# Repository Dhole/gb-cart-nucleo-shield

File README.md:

# Game Boy Cart NUCLEO Shield

## Description

This is the design of a Shield for NUCLEO STM32 development boards (also known
as STM32 NUCLEO Morpho) to connect Game Boy cartridges.

This PCB is meant to be used with my Game Boy Cart reader/writer:

- [gb-rw-stm32f411](https://github.com/Dhole/gb-rw-stm32f411)
- [gb-rw-host](https://github.com/Dhole/gb-rw-host)

## Pictures

## Components

Prices are estimations taken from AliExpress (except when stated explicitly)

- 2 x 6 pin toggle switch (~ 2 x 1.3 EUR / 10)

- 2 x 40 pin header connector strip, 2.54m spacing (~ 2 x 1.03 EUR / 10)
  - You will need to cut the strips into: 2 x 17 pins, 2 x 19 pins

- 1 x GBA slot (~ 1 x 7.02 EUR / 5)

The firmware is implemented to work on the NUCLEO-F411RE

- 1 x NUCLEO-F411RE (1 x 11.48 EUR at [eu.mouser.com](https://eu.mouser.com))

I ordered the manufacture of the board at JLCPCB with great results
- 1 x 2 layer PCB board (~ 1 x 10 EUR / 10 with shipping included in 2018)

## Attributions

The design this PCB is based on an [STM32 NUCLEO Morpho template made by
mobilinkd](https://github.com/mobilinkd/stm-morpho-template) published under
the MIT License.

The Game Boy cartridge slot component used in the PCB is taken from the [KiCad libraries by gekkio](https://github.com/Gekkio/gekkio-kicad-libs) published under the 
[Creative Commons Attribution license](https://creativecommons.org/licenses/by/4.0/)

## License

I'm publishing the rest of the work under the [Creative Commons Attribution-ShareAlike license](https://creativecommons.org/licenses/by-sa/4.0/).

**CC BY-SA**

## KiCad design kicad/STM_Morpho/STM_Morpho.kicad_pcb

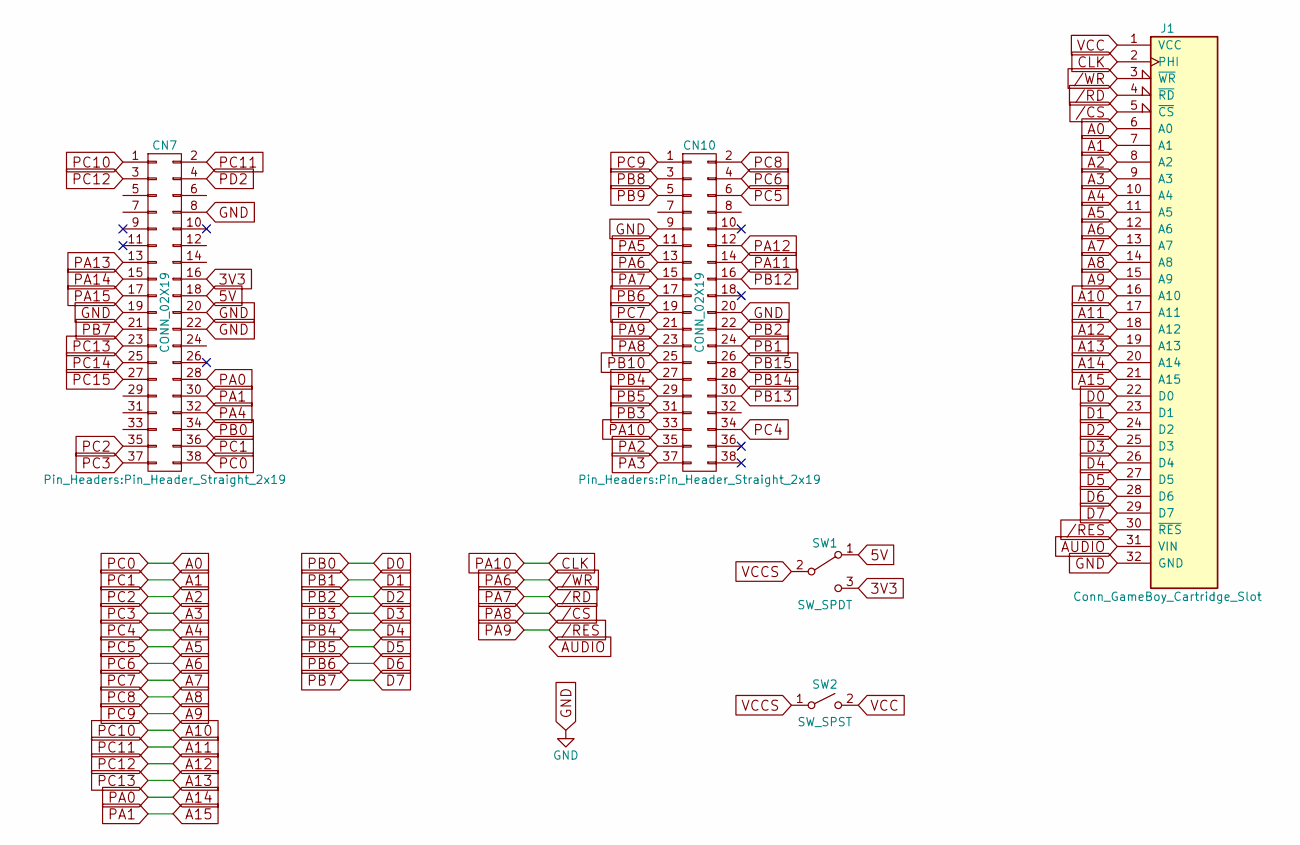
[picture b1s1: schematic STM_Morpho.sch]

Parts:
CN7, CN10: CONN_02X19; Pin_Header_Straight_2x19
J1: Conn_GameBoy_Cartridge_Slot; GameBoy_Cartridge_Slot_DSLite
SW1: SW_SPDT; SW_CuK_JS202011CQN_DPDT_Straight
SW2: SW_SPST; SW_CuK_JS202011CQN_DPDT_Straight

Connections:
3V3: CN7.16, SW1.3 (C)
5V: CN7.18, SW1.1 (A)
/CS: CN10.23, J1.5 (~CS)
/RD: CN10.15, J1.4 (~RD)
/RES: CN10.21, J1.30 (~RES)
/WR: CN10.13, J1.3 (~WR)
A0: CN7.38, J1.6 (A0)
A1: CN7.36, J1.7 (A1)
A2: CN7.35, J1.8 (A2)
A3: CN7.37, J1.9 (A3)
A4: CN10.34, J1.10 (A4)
A5: CN10.6, J1.11 (A5)
A6: CN10.4, J1.12 (A6)
A7: CN10.19, J1.13 (A7)
A8: CN10.2, J1.14 (A8)
A9: CN10.1, J1.15 (A9)
A10: CN7.1, J1.16 (A10)
A11: CN7.2, J1.17 (A11)
A12: CN7.3, J1.18 (A12)
A13: CN7.23, J1.19 (A13)
A14: CN7.28, J1.20 (A14)
A15: CN7.30, J1.21 (A15)
AUDIO: J1.31 (VIN)
CLK: CN10.33, J1.2 (PHI)
D0: CN7.34, J1.22 (D0)
D1: CN10.24, J1.23 (D1)
D2: CN10.22, J1.24 (D2)
D3: CN10.31, J1.25 (D3)
D4: CN10.27, J1.26 (D4)
D5: CN10.29, J1.27 (D5)
D6: CN10.17, J1.28 (D6)
D7: CN7.21, J1.29 (D7)
GND: CN7.8, CN7.19, CN7.20, CN7.22, CN10.9, CN10.20, J1.32 (GND)
PA4: CN7.32
PA5: CN10.11
PA11: CN10.14
PA12: CN10.12
PA13: CN7.13
PA14: CN7.15
PA15: CN7.17
PB8: CN10.3
PB9: CN10.5
PB10: CN10.25
PB12: CN10.16
PB13: CN10.30
PB14: CN10.28
PB15: CN10.26
PC14: CN7.25
PC15: CN7.27
PD2: CN7.4
VCC: J1.1 (VCC), SW2.2 (B)
VCCS: SW1.2 (B), SW2.1 (A)

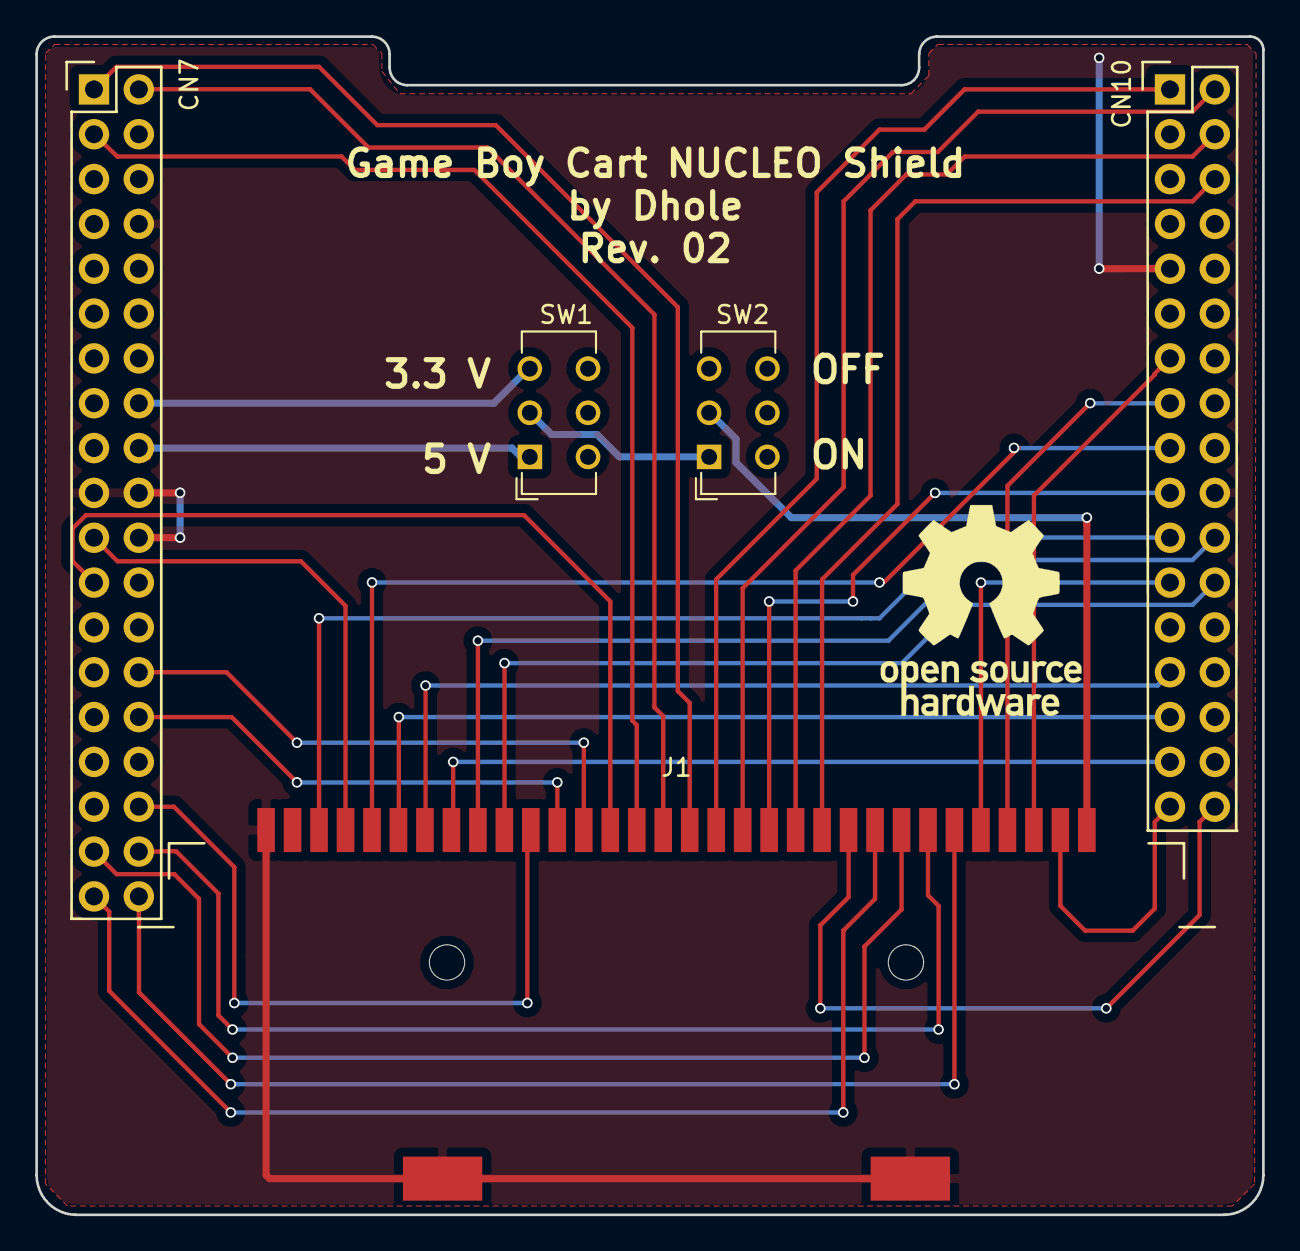
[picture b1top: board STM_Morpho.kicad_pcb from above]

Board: 2 copper layers, 69.5 x 66.8 mm, 5 parts (0 on the bottom side), 34 nets.

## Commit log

2018-03-17 Use submodule for Gekkio Kicad libs
2018-11-27 Use different GBA cart slot
2020-10-06 Add images to README
